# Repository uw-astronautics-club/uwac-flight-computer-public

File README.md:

# uwac-flight-computer
Hardware design of the UWAC open source flight computer

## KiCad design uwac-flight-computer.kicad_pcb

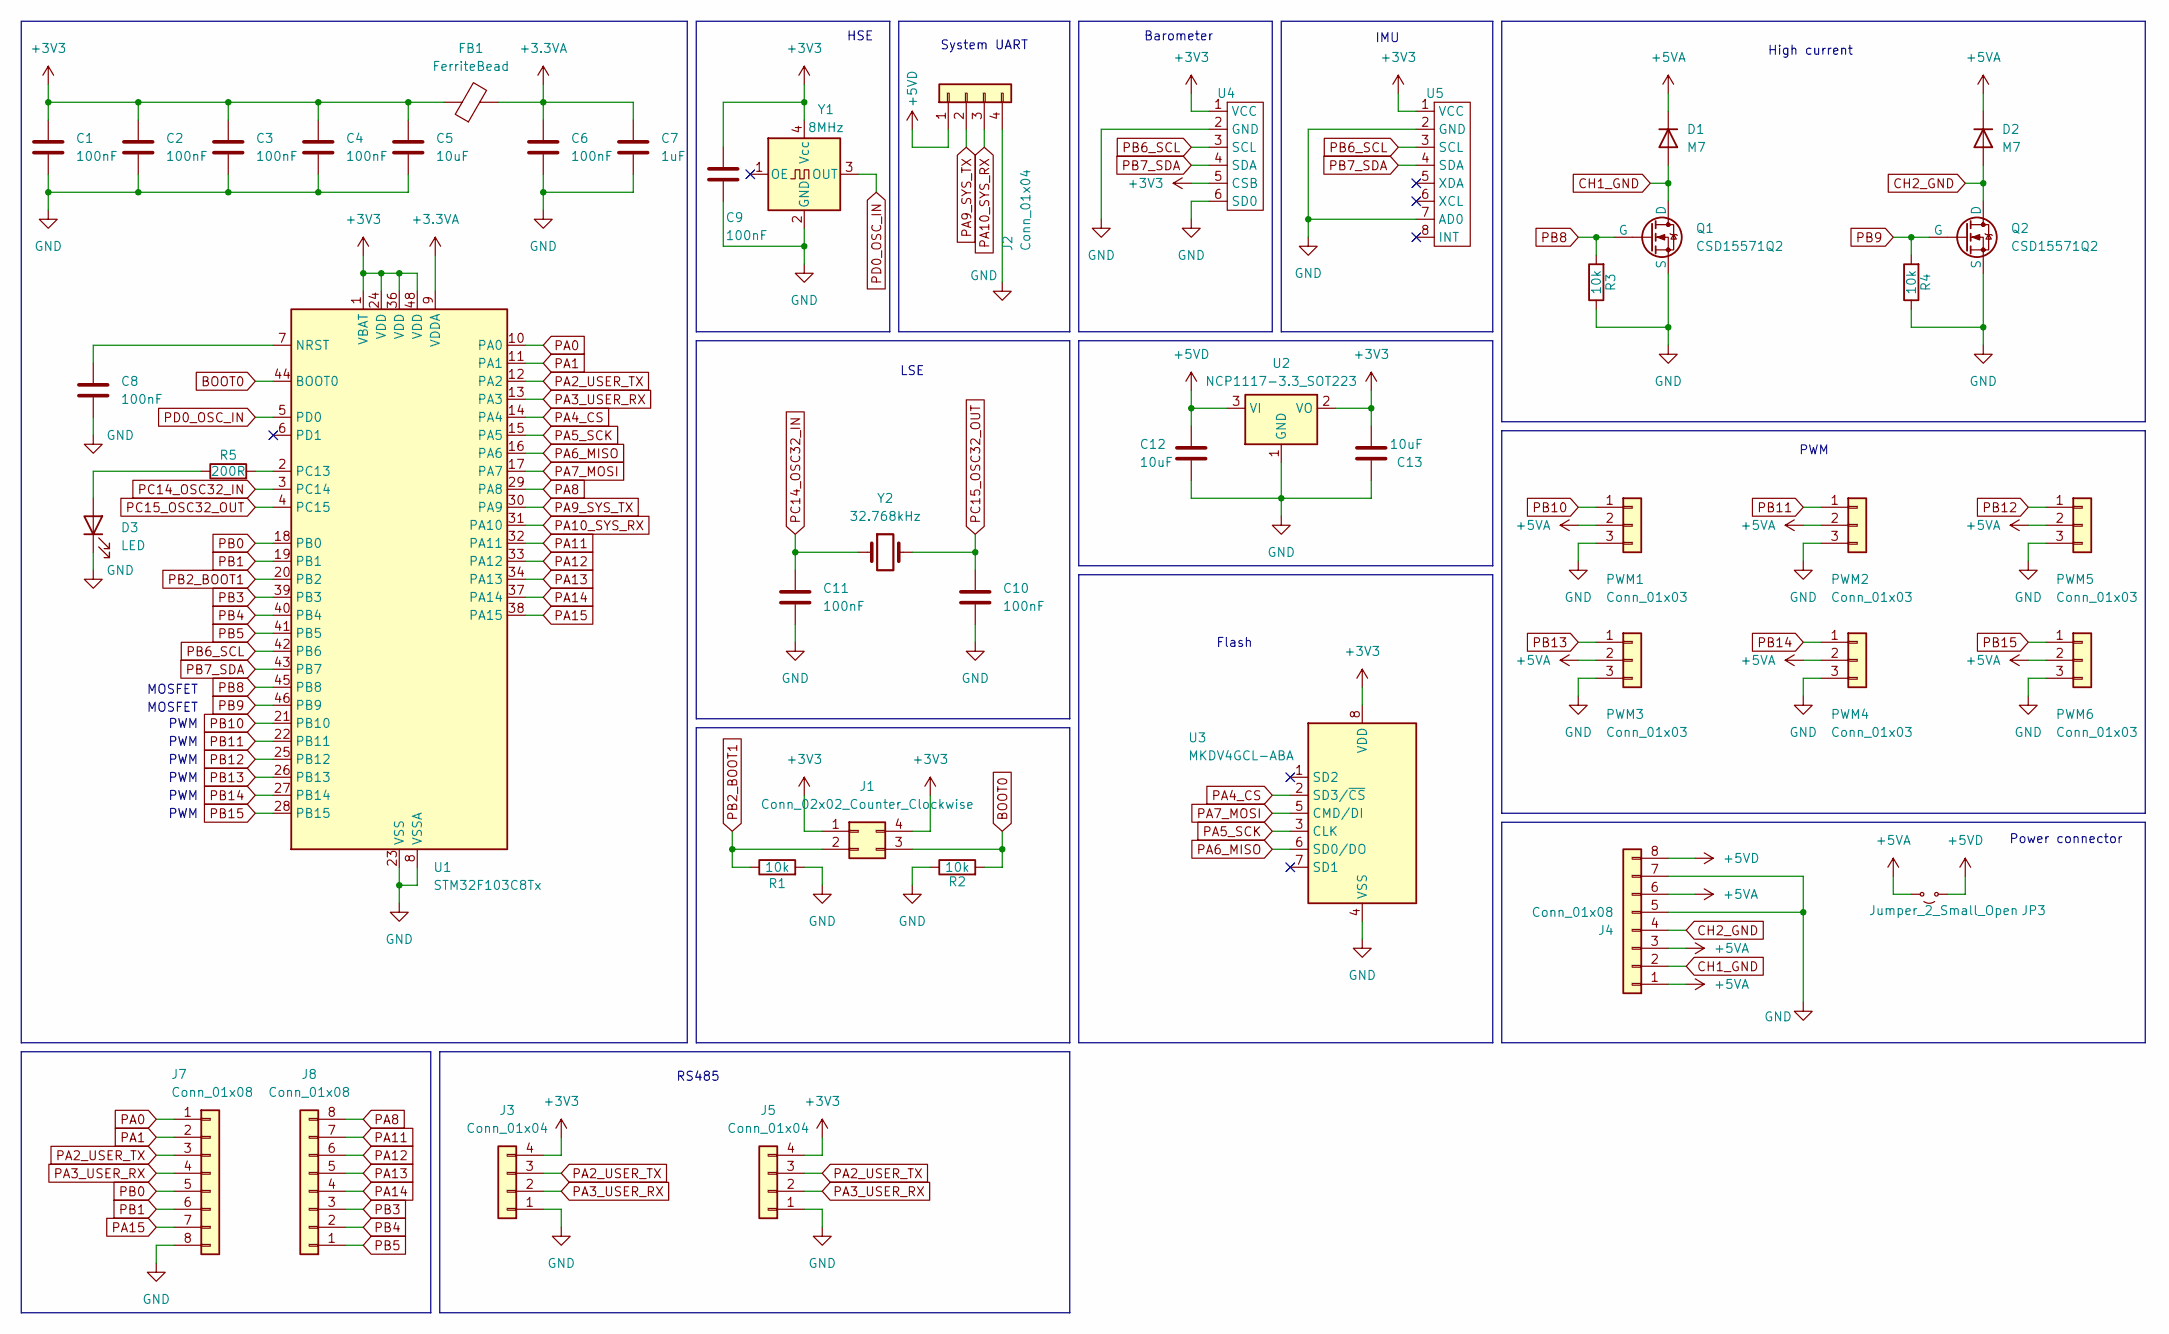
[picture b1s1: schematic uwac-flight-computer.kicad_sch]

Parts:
C1, C2, C3, C4, C6, C8, C9, C10, C11: 100nF; C_0402_1005Metric; LCSC C1525
C5, C12, C13: 10uF; C_0402_1005Metric; LCSC C15525
C7: 1uF; C_0402_1005Metric; LCSC C52923
D1, D2: M7; D_SMA; LCSC C95872
D3: LED; LED_0603_1608Metric; LCSC C2290
FB1: FerriteBead; C_0603_1608Metric; LCSC C1002
J1: Conn_02x02_Counter_Clockwise; PinHeader_2x02_P2.54mm_Vertical
J2, J5: Conn_01x04; PinHeader_1x04_P2.54mm_Vertical
J3: Conn_01x04; TerminalBlock_Xinya_XY308-2.54-4P_1x04_P2.54mm_Horizontal
J4: Conn_01x08; TerminalBlock_Xinya_XY308-2.54-8P_1x08_P2.54mm_Horizontal
J7, J8: Conn_01x08; PinHeader_1x08_P1.00mm_Vertical
JP3: Jumper_2_Small_Open; SolderJumper-2_P1.3mm_Open_Pad1.0x1.5mm
PWM1, PWM2, PWM3, PWM4, PWM5, PWM6: Conn_01x03; PWM
Q1, Q2: CSD15571Q2; corrected_texas_DQK; LCSC C412825
R1, R2, R3, R4: 10k; R_0402_1005Metric; LCSC C25744
R5: 200R; R_0402_1005Metric; LCSC C25087
U1: STM32F103C8Tx; LQFP-48_7x7mm_P0.5mm; LCSC C8734
U2: NCP1117-3.3_SOT223; SOT-223-3_TabPin2; LCSC C26537
U3: MKDV4GCL-ABA; LGA-8_8x6mm_P1.27mm; LCSC C6152618
U4: generic_bmp280_module
U5: generic_mpu6050_module
Y1: 8MHz; Crystal_SMD_2016-4Pin_2.0x1.6mm; LCSC C881716
Y2: 32.768kHz; Crystal_SMD_MicroCrystal_CM9V-T1A-2Pin_1.6x1.0mm; LCSC C1985550

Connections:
+3.3VA: C6.1, C7.1, FB1.2, U1.9 (VDDA)
+3V3: C1.1, C2.1, C3.1, C4.1, C5.1, C9.1, C13.2, FB1.1, J1.1, J1.4, J3.4, J5.4, U1.1 (VBAT), U1.24 (VDD), U1.36 (VDD), U1.48 (VDD), U2.2 (VO), U3.8 (VDD), U4.1 (VCC), U4.5 (CSB), U5.1 (VCC), Y1.4 (Vcc)
+5VA: D1.1 (K), D2.1 (K), J4.1, J4.3, J4.6, JP3.2 (B), PWM1.2, PWM2.2, PWM3.2, PWM4.2, PWM5.2, PWM6.2
+5VD: C12.1, J2.1, J4.8, JP3.1 (A), U2.3 (VI)
BOOT0: J1.3, R2.2, U1.44 (BOOT0)
CH1_GND: D1.2 (A), J4.2, Q1.1 (D)
CH2_GND: D2.2 (A), J4.4, Q2.1 (D)
GND: C1.2, C2.2, C3.2, C4.2, C5.2, C6.2, C7.2, C8.2, C9.2, C10.2, C11.2, C12.2, C13.1, D3.1 (K), J2.4, J3.1, J4.5, J4.7, J5.1, J7.8, PWM1.3, PWM2.3, PWM3.3, PWM4.3, PWM5.3, PWM6.3, Q1.3 (S), Q2.3 (S), R1.2, R2.1, R3.1, R4.1, U1.8 (VSSA), U1.23 (VSS), U1.35 (VSS), U1.47 (VSS), U2.1 (GND), U3.4 (VSS), U4.2 (GND), U4.6 (SD0), U5.2 (GND), U5.7 (AD0), Y1.2 (GND)
unnamed: D3.2 (A), R5.1
unnamed: C8.1, U1.7 (NRST)
unnamed: R5.2, U1.2 (PC13)
PA0: J7.1, U1.10 (PA0)
PA1: J7.2, U1.11 (PA1)
PA2_USER_TX: J3.3, J5.3, J7.3, U1.12 (PA2)
PA3_USER_RX: J3.2, J5.2, J7.4, U1.13 (PA3)
PA4_CS: U1.14 (PA4), U3.2 (SD3/~CS)
PA5_SCK: U1.15 (PA5), U3.3 (CLK)
PA6_MISO: U1.16 (PA6), U3.6 (SD0/DO)
PA7_MOSI: U1.17 (PA7), U3.5 (CMD/DI)
PA8: J8.8, U1.29 (PA8)
PA9_SYS_TX: J2.2, U1.30 (PA9)
PA10_SYS_RX: J2.3, U1.31 (PA10)
PA11: J8.7, U1.32 (PA11)
PA12: J8.6, U1.33 (PA12)
PA13: J8.5, U1.34 (PA13)
PA14: J8.4, U1.37 (PA14)
PA15: J7.7, U1.38 (PA15)
PB0: J7.5, U1.18 (PB0)
PB1: J7.6, U1.19 (PB1)
PB2_BOOT1: J1.2, R1.1, U1.20 (PB2)
PB3: J8.3, U1.39 (PB3)
PB4: J8.2, U1.40 (PB4)
PB5: J8.1, U1.41 (PB5)
PB6_SCL: U1.42 (PB6), U4.3 (SCL), U5.3 (SCL)
PB7_SDA: U1.43 (PB7), U4.4 (SDA), U5.4 (SDA)
PB8: Q1.2 (G), R3.2, U1.45 (PB8)
PB9: Q2.2 (G), R4.2, U1.46 (PB9)
PB10: PWM1.1, U1.21 (PB10)
PB11: PWM2.1, U1.22 (PB11)
PB12: PWM5.1, U1.25 (PB12)
PB13: PWM3.1, U1.26 (PB13)
PB14: PWM4.1, U1.27 (PB14)
PB15: PWM6.1, U1.28 (PB15)
PC14_OSC32_IN: C11.1, U1.3 (PC14), Y2.1
PC15_OSC32_OUT: C10.1, U1.4 (PC15), Y2.2
PD0_OSC_IN: U1.5 (PD0), Y1.3 (OUT)

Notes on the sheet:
HSE
Barometer
PWM
System UART
Power connector
High current
RS485
LSE
Flash
MOSFET
IMU

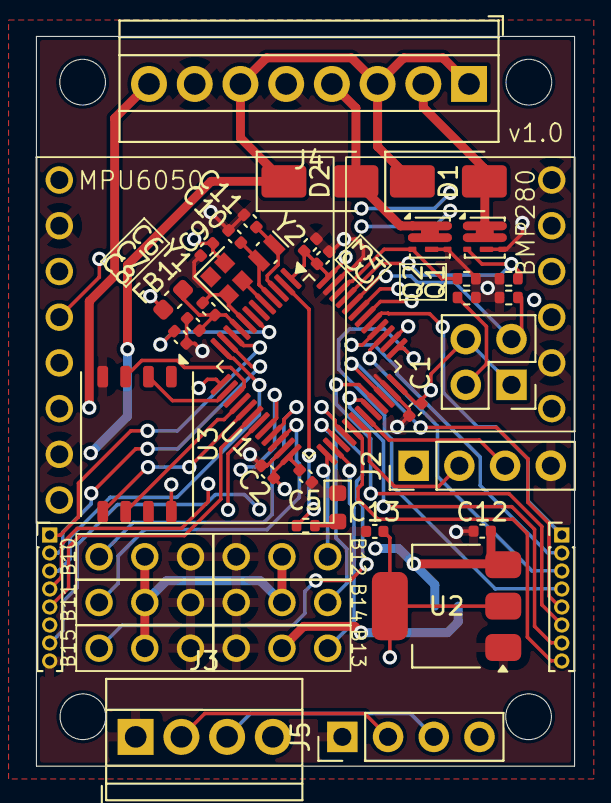
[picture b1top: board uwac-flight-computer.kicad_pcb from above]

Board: 4 copper layers, 29.9 x 40.5 mm, 45 parts (1 on the bottom side), 46 nets.

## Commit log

2025-03-26 Release v1.0
